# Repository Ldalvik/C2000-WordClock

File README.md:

# TI-F2806x-WordClock
A replication of my "RGB-WordClock" on a TI-C2000 F28069M, written in bare metal C.

## Software
Since there is no official HAL for this device, this project required deep digging into data sheets. I threw together a small library that does basic things like starting/stopping interrupts, interfacing the main loop to be more arduino-like, and all the other IO related things I would need like digital in/out and muxing. The most important part was setting the SPI peripheral to work with a real-time clock, specifically the DS1302. After reading the datasheet, I was able to get the correct settings (baud-rate, polarity/phase, etc) and communicate back and forth with the RTC. I created a full library for it to work with this F2806x as well.

# Hardware

For the PCB, I used KiCAD and made a shield for the F28069. The LEDs I decided on were extremely small (about a millimeter), and a microscope was needed to place them correctly. Other components consist of the DS1302, resistors for each LED, capacitor for filtering, 6pF 32.768khz crystal, and a small coin cell battery for a few days of time keeping while unplugged.

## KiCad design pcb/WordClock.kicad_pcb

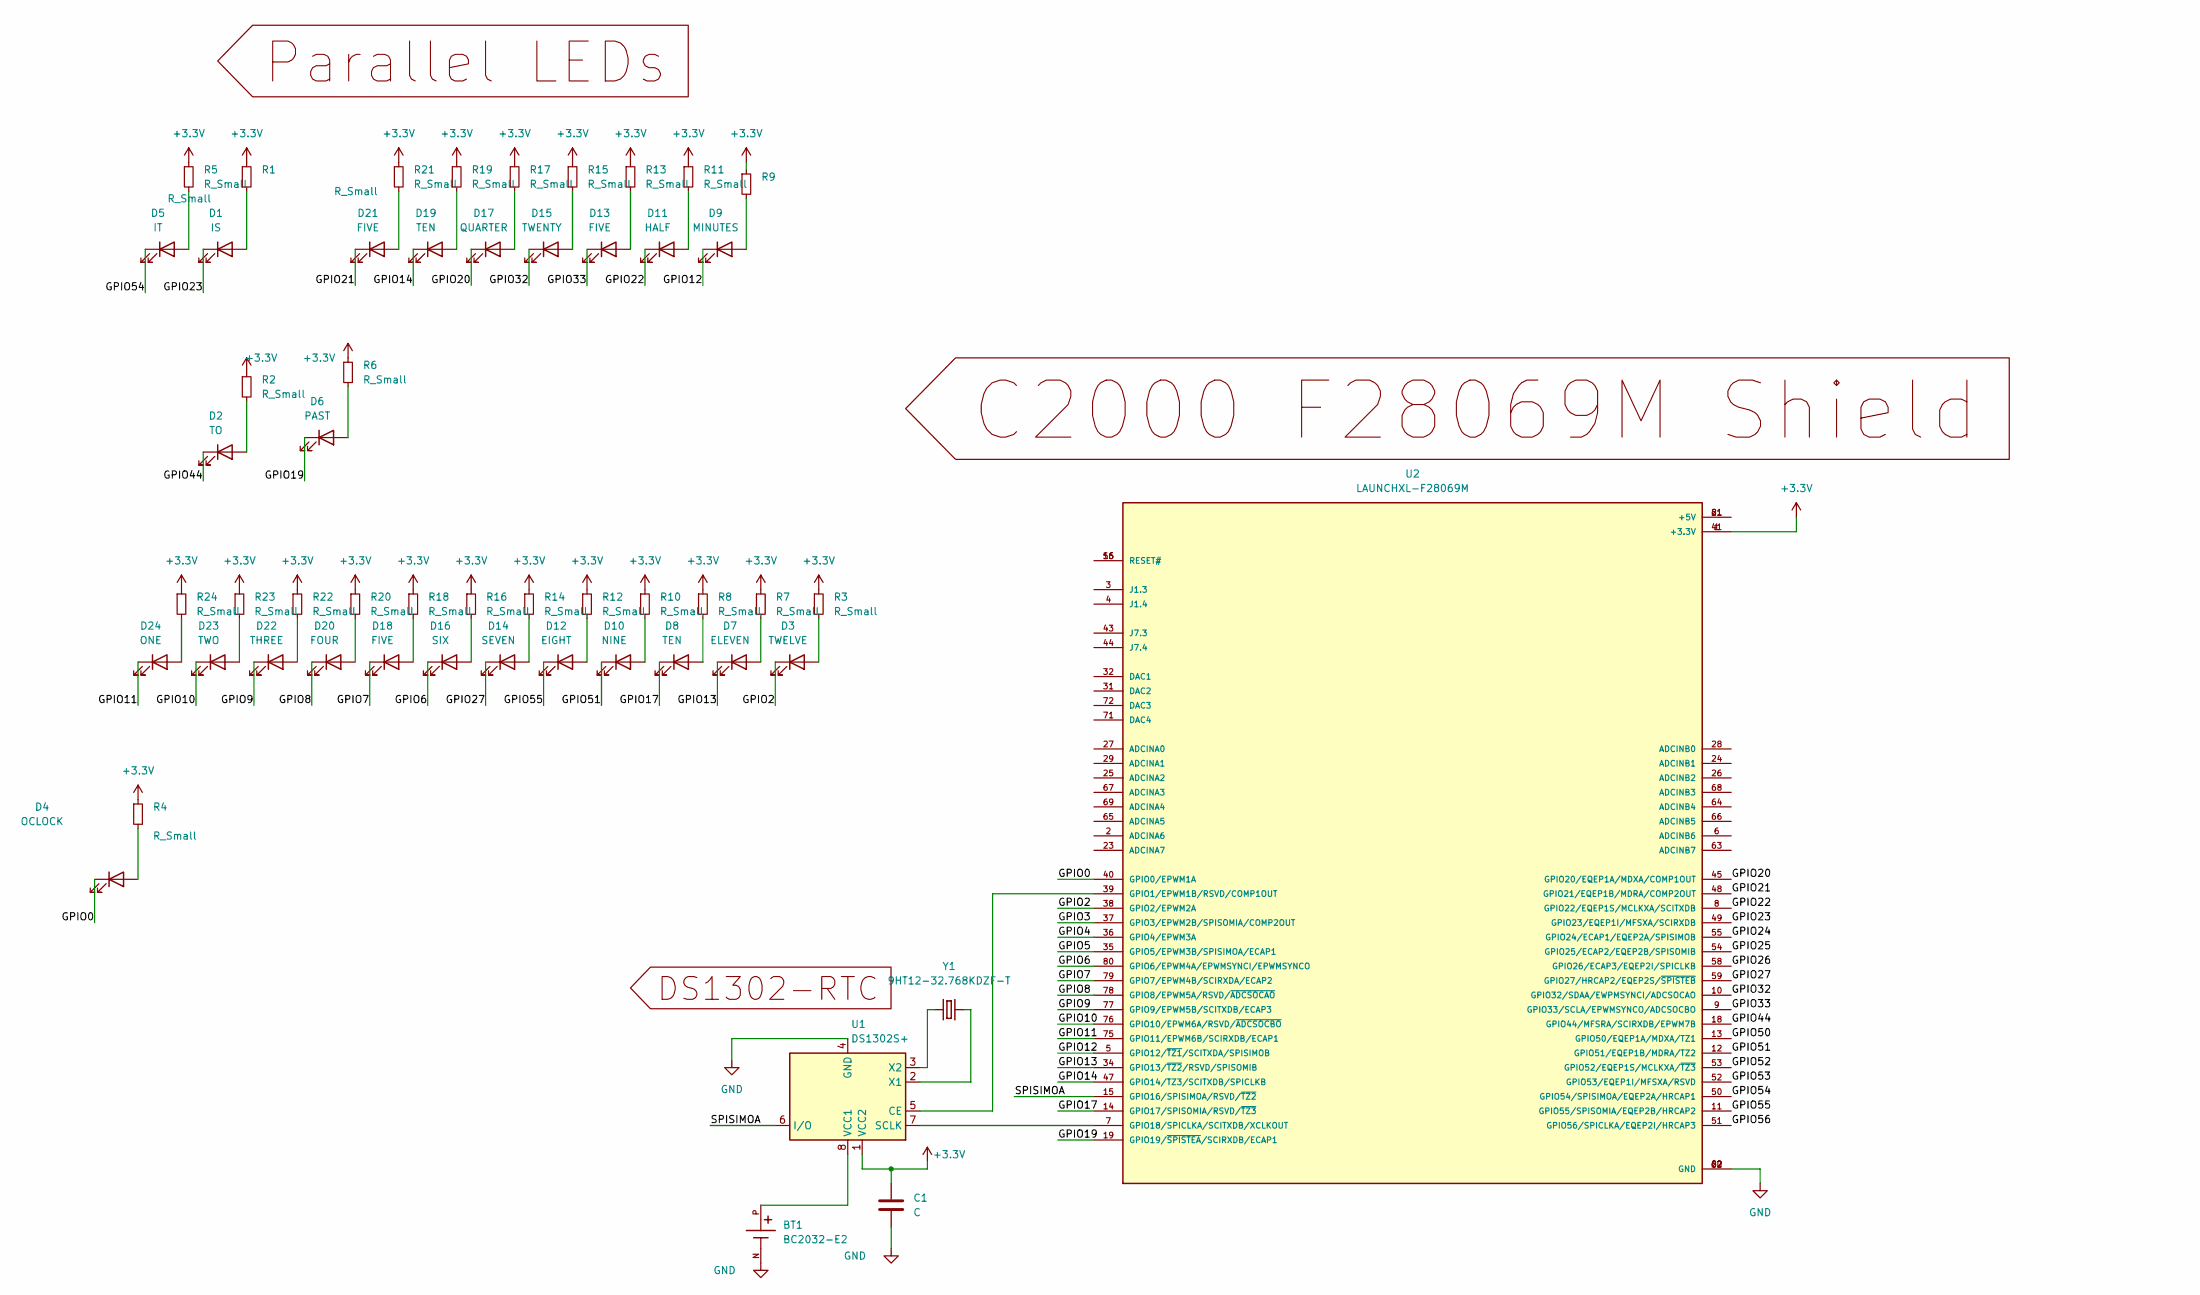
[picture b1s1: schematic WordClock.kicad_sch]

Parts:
BT1: BC2032-E2; MPD_BC2032-E2; PARTREV D
C1: C; C_0805_2012Metric
D1: IS; LED_0201_0603Metric_Pad0.64x0.40mm_HandSolder
D2: TO; LED_0201_0603Metric_Pad0.64x0.40mm_HandSolder
D3: TWELVE; LED_0201_0603Metric_Pad0.64x0.40mm_HandSolder
D4: OCLOCK; LED_0201_0603Metric_Pad0.64x0.40mm_HandSolder
D5: IT; LED_0201_0603Metric_Pad0.64x0.40mm_HandSolder
D6: PAST; LED_0201_0603Metric_Pad0.64x0.40mm_HandSolder
D7: ELEVEN; LED_0201_0603Metric_Pad0.64x0.40mm_HandSolder
D8, D19: TEN; LED_0201_0603Metric_Pad0.64x0.40mm_HandSolder
D9: MINUTES; LED_0201_0603Metric_Pad0.64x0.40mm_HandSolder
D10: NINE; LED_0201_0603Metric_Pad0.64x0.40mm_HandSolder
D11: HALF; LED_0201_0603Metric_Pad0.64x0.40mm_HandSolder
D12: EIGHT; LED_0201_0603Metric_Pad0.64x0.40mm_HandSolder
D13, D18, D21: FIVE; LED_0201_0603Metric_Pad0.64x0.40mm_HandSolder
D14: SEVEN; LED_0201_0603Metric_Pad0.64x0.40mm_HandSolder
D15: TWENTY; LED_0201_0603Metric_Pad0.64x0.40mm_HandSolder
D16: SIX; LED_0201_0603Metric_Pad0.64x0.40mm_HandSolder
D17: QUARTER; LED_0201_0603Metric_Pad0.64x0.40mm_HandSolder
D20: FOUR; LED_0201_0603Metric_Pad0.64x0.40mm_HandSolder
D22: THREE; LED_0201_0603Metric_Pad0.64x0.40mm_HandSolder
D23: TWO; LED_0201_0603Metric_Pad0.64x0.40mm_HandSolder
D24: ONE; LED_0201_0603Metric_Pad0.64x0.40mm_HandSolder
R1, R2, R3, R4, R5, R6, R7, R8, R9, R10, R11, R12, R13, R14, R15, R16, R17, R18, R19, R20, R21, R22, R23, R24: R_Small; R_0805_2012Metric_Pad1.20x1.40mm_HandSolder
U1: DS1302S+; SO-8_5.3x6.2mm_P1.27mm
U2: LAUNCHXL-F28069M; TI_LAUNCHXL-F28069M; PARTREV B
Y1: 9HT12-32.768KDZF-T; XTAL160X100X50

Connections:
+3.3V: C1.1, R1.1, R2.1, R3.1, R4.1, R5.1, R6.1, R7.1, R8.1, R9.1, R10.1, R11.1, R12.1, R13.1, R14.1, R15.1, R16.1, R17.1, R18.1, R19.1, R20.1, R21.1, R22.1, R23.1, R24.1, U1.1 (VCC2), U2.1 (+3.3V), U2.41 (+3.3V)
/GPIO0: D4.1 (K), U2.40 (GPIO0/EPWM1A)
/GPIO2: D3.1 (K), U2.38 (GPIO2/EPWM2A)
/GPIO3: U2.37 (GPIO3/EPWM2B/SPISOMIA/COMP2OUT)
/GPIO4: U2.36 (GPIO4/EPWM3A)
/GPIO5: U2.35 (GPIO5/EPWM3B/SPISIMOA/ECAP1)
/GPIO6: D16.1 (K), U2.80 (GPIO6/EPWM4A/EPWMSYNCI/EPWMSYNCO)
/GPIO7: D18.1 (K), U2.79 (GPIO7/EPWM4B/SCIRXDA/ECAP2)
/GPIO8: D20.1 (K), U2.78 (GPIO8/EPWM5A/RSVD/~ADCSOCAO)
/GPIO9: D22.1 (K), U2.77 (GPIO9/EPWM5B/SCITXDB/ECAP3)
/GPIO10: D23.1 (K), U2.76 (GPIO10/EPWM6A/RSVD/~ADCSOCBO)
/GPIO11: D24.1 (K), U2.75 (GPIO11/EPWM6B/SCIRXDB/ECAP1)
/GPIO12: D9.1 (K), U2.5 (GPIO12/~TZ1/SCITXDA/SPISIMOB)
/GPIO13: D7.1 (K), U2.34 (GPIO13/~TZ2/RSVD/SPISOMIB)
/GPIO14: D19.1 (K), U2.47 (GPIO14/TZ3/SCITXDB/SPICLKB)
/GPIO17: D8.1 (K), U2.14 (GPIO17/SPISOMIA/RSVD/~TZ3)
/GPIO19: D6.1 (K), U2.19 (GPIO19/~SPISTEA/SCIRXDB/ECAP1)
/GPIO20: D17.1 (K), U2.45 (GPIO20/EQEP1A/MDXA/COMP1OUT)
/GPIO21: D21.1 (K), U2.48 (GPIO21/EQEP1B/MDRA/COMP2OUT)
/GPIO22: D11.1 (K), U2.8 (GPIO22/EQEP1S/MCLKXA/SCITXDB)
/GPIO23: D1.1 (K), U2.49 (GPIO23/EQEP1I/MFSXA/SCIRXDB)
/GPIO24: U2.55 (GPIO24/ECAP1/EQEP2A/SPISIMOB)
/GPIO25: U2.54 (GPIO25/ECAP2/EQEP2B/SPISOMIB)
/GPIO26: U2.58 (GPIO26/ECAP3/EQEP2I/SPICLKB)
/GPIO27: D14.1 (K), U2.59 (GPIO27/HRCAP2/EQEP2S/~SPISTEB)
/GPIO32: D15.1 (K), U2.10 (GPIO32/SDAA/EWPMSYNCI/ADCSOCAO)
/GPIO33: D13.1 (K), U2.9 (GPIO33/SCLA/EPWMSYNCO/ADCSOCBO)
/GPIO44: D2.1 (K), U2.18 (GPIO44/MFSRA/SCIRXDB/EPWM7B)
/GPIO50: U2.13 (GPIO50/EQEP1A/MDXA/TZ1)
/GPIO51: D10.1 (K), U2.12 (GPIO51/EQEP1B/MDRA/TZ2)
/GPIO52: U2.53 (GPIO52/EQEP1S/MCLKXA/~TZ3)
/GPIO53: U2.52 (GPIO53/EQEP1I/MFSXA/RSVD)
/GPIO54: D5.1 (K), U2.50 (GPIO54/SPISIMOA/EQEP2A/HRCAP1)
/GPIO55: D12.1 (K), U2.11 (GPIO55/SPISOMIA/EQEP2B/HRCAP2)
/GPIO56: U2.51 (GPIO56/SPICLKA/EQEP2I/HRCAP3)
/SPISIMOA: U1.6 (I/O), U2.15 (GPIO16/SPISIMOA/RSVD/~TZ2)
GND: BT1.N, C1.2, U1.4 (GND), U2.22 (GND), U2.60 (GND), U2.62 (GND)
unnamed: BT1.P, U1.8 (VCC1)
unnamed: D1.2 (A), R1.2
unnamed: D2.2 (A), R2.2
unnamed: D3.2 (A), R3.2
unnamed: D4.2 (A), R4.2
unnamed: D5.2 (A), R5.2
unnamed: D6.2 (A), R6.2
unnamed: D7.2 (A), R7.2
unnamed: D8.2 (A), R8.2
unnamed: D9.2 (A), R9.2
unnamed: D10.2 (A), R10.2
unnamed: D11.2 (A), R11.2
unnamed: D12.2 (A), R12.2
unnamed: D13.2 (A), R13.2
unnamed: D14.2 (A), R14.2
unnamed: D15.2 (A), R15.2
unnamed: D16.2 (A), R16.2
unnamed: D17.2 (A), R17.2
unnamed: D18.2 (A), R18.2
unnamed: D19.2 (A), R19.2
unnamed: D20.2 (A), R20.2
unnamed: D21.2 (A), R21.2
unnamed: D22.2 (A), R22.2
unnamed: D23.2 (A), R23.2
unnamed: D24.2 (A), R24.2
unnamed: U1.2 (X1), Y1.2
unnamed: U1.3 (X2), Y1.1
unnamed: U1.5 (CE), U2.39 (GPIO1/EPWM1B/RSVD/COMP1OUT)
unnamed: U1.7 (SCLK), U2.7 (GPIO18/SPICLKA/SCITXDB/XCLKOUT)
unnamed: U2.16 (RESET#), U2.56 (RESET#)
unnamed: U2.21 (+5V), U2.61 (+5V)

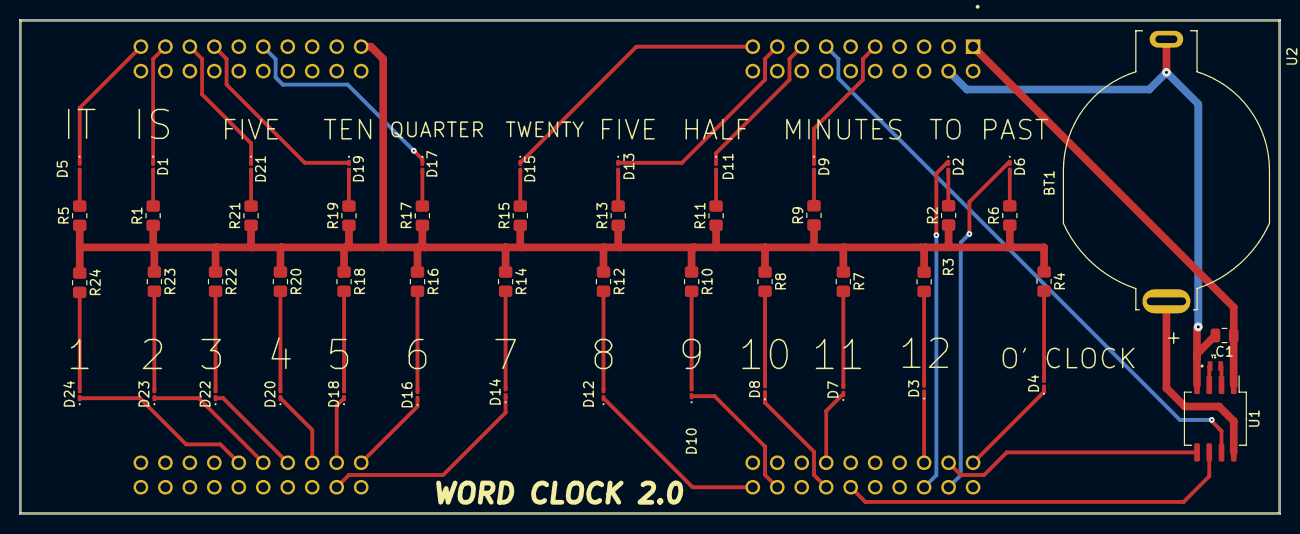
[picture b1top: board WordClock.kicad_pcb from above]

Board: 2 copper layers, 130.8 x 51.3 mm, 53 parts (0 on the bottom side), 58 nets.

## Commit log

2023-03-23 Add project libraries + F28069 drivers to GitHub
2023-03-23 Create t
2023-03-23 Add TI F2806x driver header files
2023-03-23 Add TI F2806x driver source files
2023-05-11 Added PCB layouts
2023-05-11 Rename WordClock.kicad_sch to pcb/WordClock.kicad_sch
2023-05-11 Rename WordClock.kicad_pro to pcb/WordClock.kicad_pro
2023-05-11 Rename WordClock.kicad_pcb to pcb/WordClock.kicad_pcb
